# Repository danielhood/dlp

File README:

DLP - Dirty 'Lil Penguin Synth
------------------------------

- Inital conception around 2010.

- First working module was the distoriton module at the end of 2010.

- MIDI to CV module completed Feb 2012.

- Saw/Square oscillaror with 2 channel ouput mixer, mounted in toolbox completed March 2012.

- v2.0 started April 2015 which is bascially eurorack version of most of the modules

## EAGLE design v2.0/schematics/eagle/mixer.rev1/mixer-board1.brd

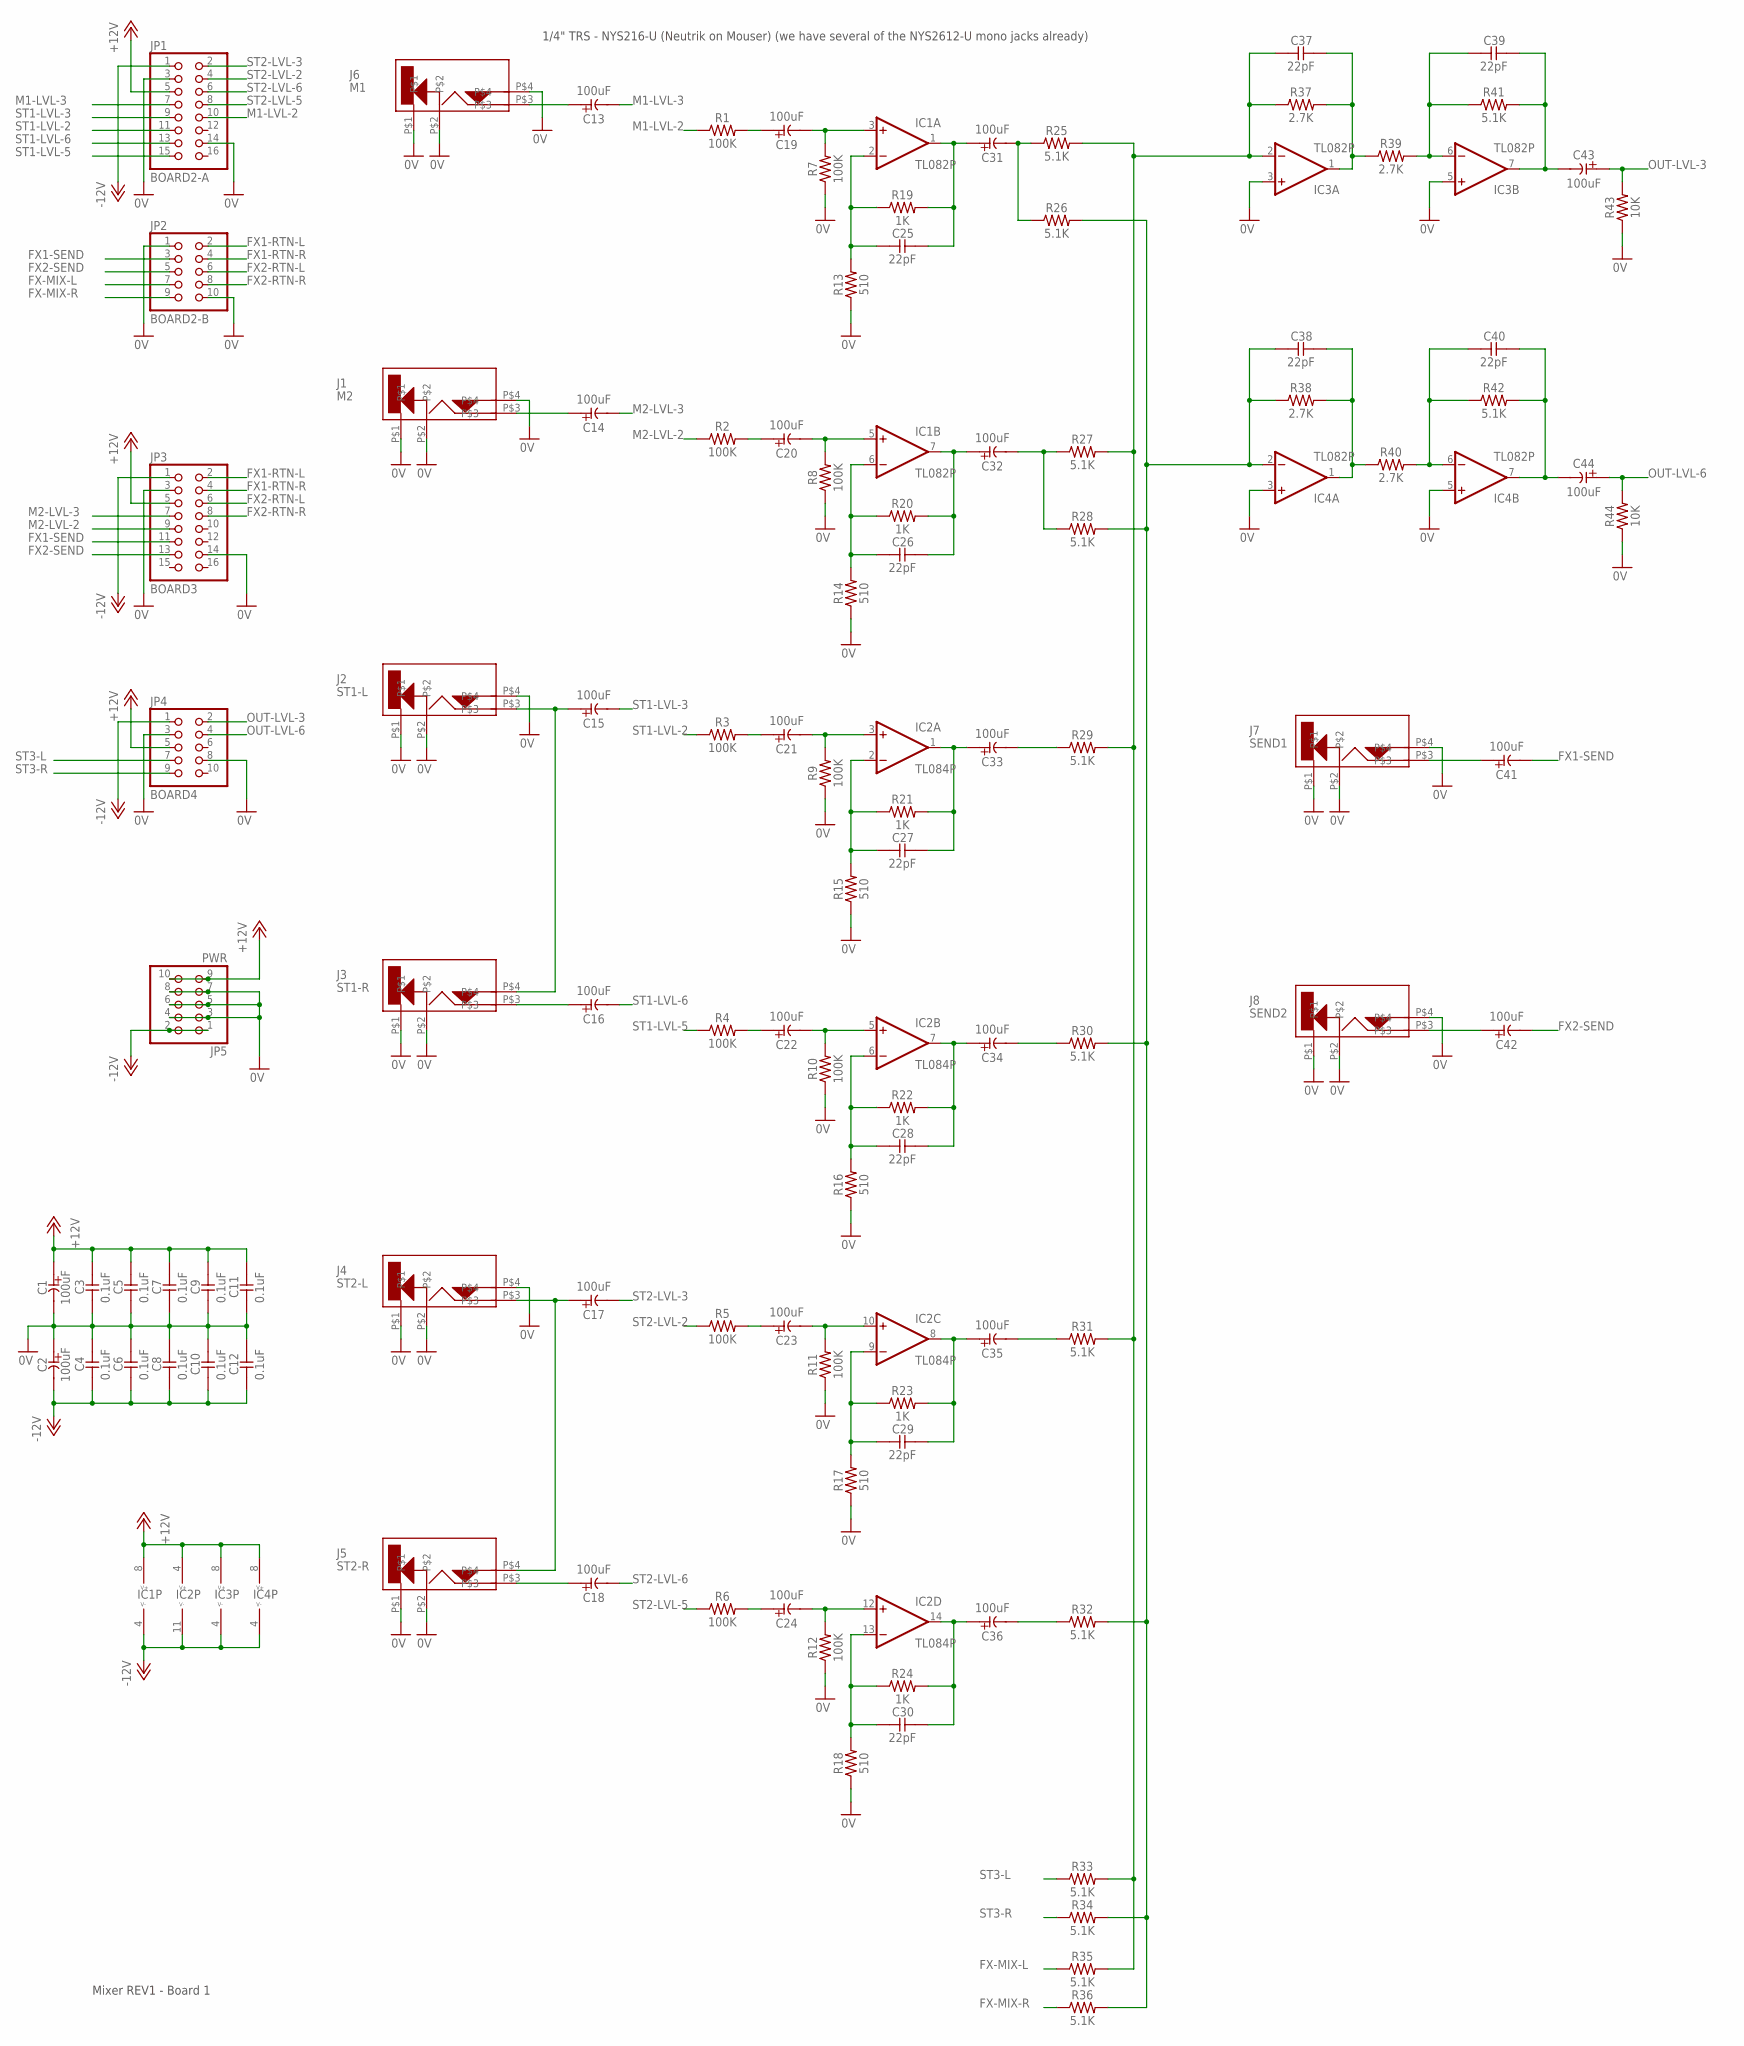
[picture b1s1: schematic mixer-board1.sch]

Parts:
C1, C2, C13, C14, C15, C16, C17, C18, C19, C20, C21, C22, C23, C24, C31, C32, C33, C34, C35, C36, C41, C42, C43, C44: 100uF; E5-8,5
C3, C4, C5, C6, C7, C8, C9, C10, C11, C12: 0.1uF; C025-024X044
C25, C26, C27, C28, C29, C30, C37, C38, C39, C40: 22pF; C025-024X044
IC1, IC3, IC4: TL082P; DIL08
IC2: TL084P; DIL14
J1: M2; CL1384
J2: ST1-L; CL1384
J3: ST1-R; CL1384
J4: ST2-L; CL1384
J5: ST2-R; CL1384
J6: M1; CL1384
J7: SEND1; CL1384
J8: SEND2; CL1384
JP1: BOARD2-A; 2X08
JP2: BOARD2-B; 2X05
JP3: BOARD3; 2X08
JP4: BOARD4; 2X05
JP5: PWR; 2X05
R1, R2, R3, R4, R5, R6, R7, R8, R9, R10, R11, R12: 100K; 0207/7
R13, R14, R15, R16, R17, R18: 510; 0207/7
R19, R20, R21, R22, R23, R24: 1K; 0207/7
R25, R26, R27, R28, R29, R30, R31, R32, R33, R34, R35, R36, R41, R42: 5.1K; 0207/7
R37, R38, R39, R40: 2.7K; 0207/7
R43, R44: 10K; 0207/7

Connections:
0V: C1.-, C2.+, C3.2, C4.1, C5.2, C6.1, C7.2, C8.1, C9.2, C10.1, C11.2, C12.1, IC3.3 (+IN), IC3.5 (+IN), IC4.3 (+IN), IC4.5 (+IN), J1.P$1, J1.P$2, J1.P$4, J2.P$1, J2.P$2, J2.P$4, J3.P$1, J3.P$2, J4.P$1, J4.P$2, J4.P$4, J5.P$1, J5.P$2, J6.P$1, J6.P$2, J6.P$4, J7.P$1, J7.P$2, J7.P$4, J8.P$1, J8.P$2, J8.P$4, JP1.3, JP1.14, JP2.1, JP2.10, JP3.3, JP3.14, JP4.3, JP4.8, JP5.3, JP5.4, JP5.5, JP5.6, JP5.7, JP5.8, R7.1, R8.1, R9.1, R10.1, R11.1, R12.1, R13.1, R14.1, R15.1, R16.1, R17.1, R18.1, R43.1, R44.1
+12V: C1.+, C3.1, C5.1, C7.1, C9.1, C11.1, IC1.8 (V+), IC2.4 (V+), IC3.8 (V+), IC4.8 (V+), JP1.5, JP3.5, JP4.5, JP5.9, JP5.10
-12V: C2.-, C4.2, C6.2, C8.2, C10.2, C12.2, IC1.4 (V-), IC2.11 (V-), IC3.4 (V-), IC4.4 (V-), JP1.1, JP3.1, JP4.1, JP5.1, JP5.2
FX1-RTN-L: JP2.2, JP3.2
FX1-RTN-R: JP2.4, JP3.4
FX1-SEND: C41.-, JP2.3, JP3.11
FX2-RTN-L: JP2.6, JP3.6
FX2-RTN-R: JP2.8, JP3.8
FX2-SEND: C42.-, JP2.5, JP3.13
FX-MIX-L: JP2.7, R35.1
FX-MIX-R: JP2.9, R36.1
M1-LVL-2: JP1.10, R1.1
M1-LVL-3: C13.-, JP1.7
M2-LVL-2: JP3.9, R2.1
M2-LVL-3: C14.-, JP3.7
unnamed: C13.+, J6.P$3
unnamed: C25.2, IC1.2 (-IN), R13.2, R19.1
unnamed: C19.-, IC1.3 (+IN), R7.2
unnamed: C19.+, R1.2
unnamed: C25.1, C31.+, IC1.1 (OUT), R19.2
unnamed: C31.-, R25.1, R26.1
unnamed: C37.2, IC3.2 (-IN), R25.2, R27.2, R29.2, R31.2, R33.2, R35.2, R37.1
unnamed: C37.1, IC3.1 (OUT), R37.2, R39.1
unnamed: C39.2, IC3.6 (-IN), R39.2, R41.1
unnamed: C32.-, R27.1, R28.1
unnamed: C38.1, IC4.1 (OUT), R38.2, R40.1
unnamed: C40.2, IC4.6 (-IN), R40.2, R42.1
unnamed: C39.1, C43.-, IC3.7 (OUT), R41.2
unnamed: C42.+, J8.P$3
unnamed: C38.2, IC4.2 (-IN), R26.2, R28.2, R30.2, R32.2, R34.2, R36.2, R38.1
unnamed: C14.+, J1.P$3
unnamed: C15.+, J2.P$3, J3.P$4
unnamed: C40.1, C44.-, IC4.7 (OUT), R42.2
unnamed: C16.+, J3.P$3
unnamed: C17.+, J4.P$3, J5.P$4
unnamed: C18.+, J5.P$3
unnamed: C26.1, C32.+, IC1.7 (OUT), R20.2
unnamed: C26.2, IC1.6 (-IN), R14.2, R20.1
unnamed: C20.-, IC1.5 (+IN), R8.2
unnamed: C20.+, R2.2
unnamed: C41.+, J7.P$3
unnamed: C34.-, R30.1
unnamed: C33.-, R29.1
unnamed: C27.1, C33.+, IC2.1 (OUT), R21.2
unnamed: C27.2, IC2.2 (-IN), R15.2, R21.1
unnamed: C21.-, IC2.3 (+IN), R9.2
unnamed: C21.+, R3.2
unnamed: C28.1, C34.+, IC2.7 (OUT), R22.2
unnamed: C28.2, IC2.6 (-IN), R16.2, R22.1
unnamed: C22.-, IC2.5 (+IN), R10.2
unnamed: C22.+, R4.2
unnamed: C35.-, R31.1
unnamed: C29.1, C35.+, IC2.8 (OUT), R23.2
unnamed: C29.2, IC2.9 (-IN), R17.2, R23.1
unnamed: C23.-, IC2.10 (+IN), R11.2
unnamed: C23.+, R5.2
unnamed: C36.-, R32.1
unnamed: C30.1, C36.+, IC2.14 (OUT), R24.2
unnamed: C30.2, IC2.13 (-IN), R18.2, R24.1
unnamed: C24.-, IC2.12 (+IN), R12.2
unnamed: C24.+, R6.2
OUT-LVL-3: C43.+, JP4.2, R43.2
OUT-LVL-6: C44.+, JP4.4, R44.2
ST1-LVL-2: JP1.11, R3.1
ST1-LVL-3: C15.-, JP1.9
ST1-LVL-5: JP1.15, R4.1
ST1-LVL-6: C16.-, JP1.13
ST2-LVL-2: JP1.4, R5.1
ST2-LVL-3: C17.-, JP1.2
ST2-LVL-5: JP1.8, R6.1
ST2-LVL-6: C18.-, JP1.6
ST3-L: JP4.7, R33.1
ST3-R: JP4.9, R34.1

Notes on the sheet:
1/4" TRS - NYS216-U (Neutrik on Mouser) (we have several of the NYS2612-U mono jacks already)
Mixer REV1 - Board 1

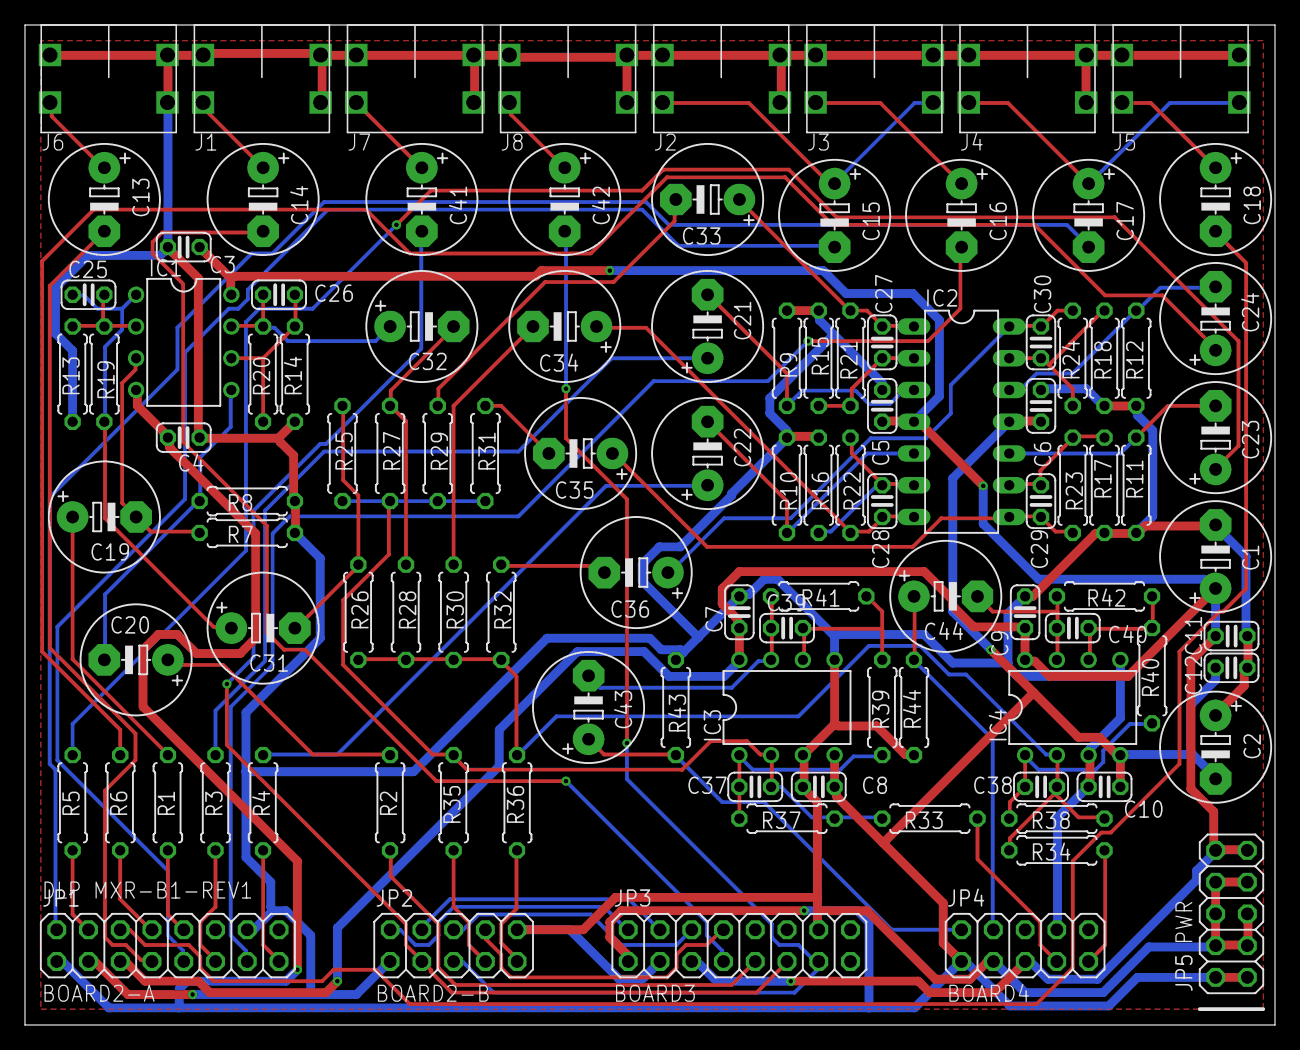
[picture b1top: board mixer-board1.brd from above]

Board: 2 copper layers, 100.0 x 80.0 mm, 105 parts (0 on the bottom side), 73 nets.

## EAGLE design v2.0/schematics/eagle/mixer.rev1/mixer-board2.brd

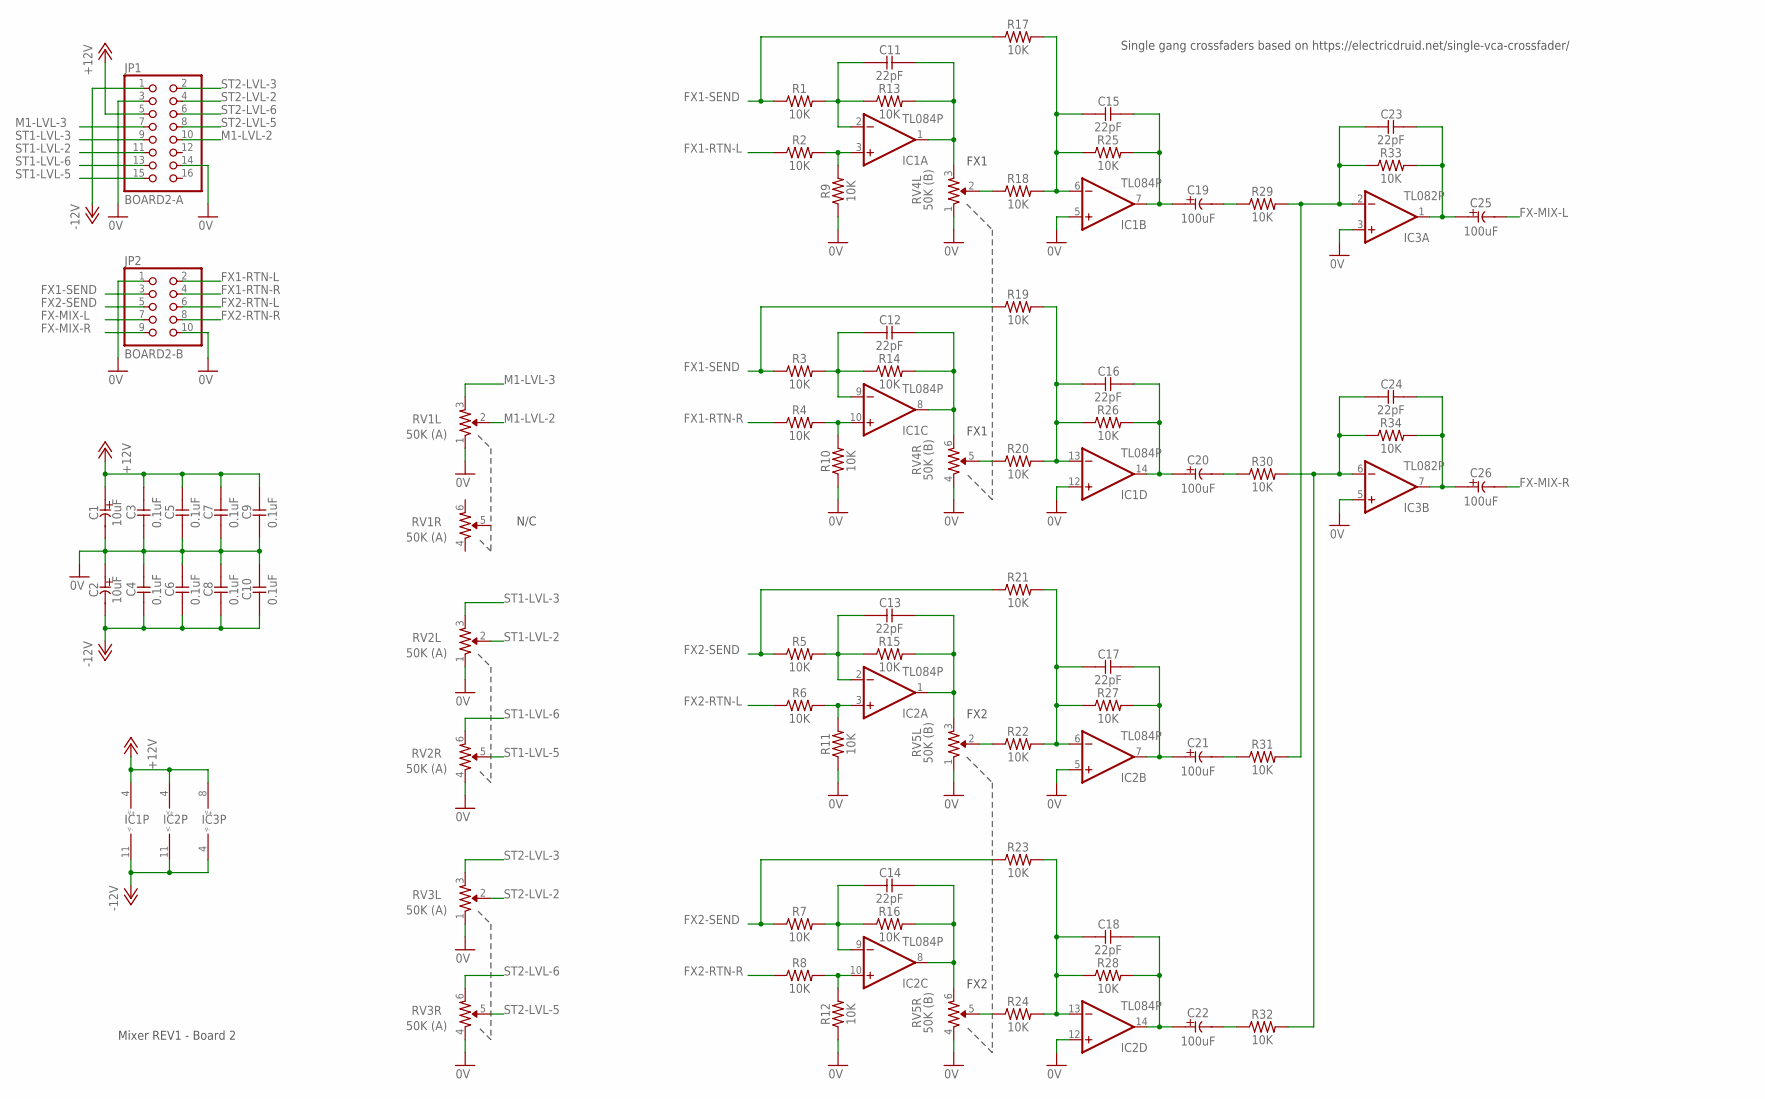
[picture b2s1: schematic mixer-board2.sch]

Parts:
C1, C2: 10uF; E2-5
C3, C4, C5, C6, C7, C8, C9, C10: 0.1uF; C025-024X044
C11, C12, C13, C14, C15, C16, C17, C18, C23, C24: 22pF; C025-024X044
C19, C20, C21, C22, C25, C26: 100uF; E5-8,5
IC1, IC2: TL084P; DIL14
IC3: TL082P; DIL08
JP1: BOARD2-A; 2X08
JP2: BOARD2-B; 2X05
R1, R2, R3, R4, R5, R6, R7, R8, R9, R10, R11, R12, R13, R14, R15, R16, R17, R18, R19, R20, R21, R22, R23, R24, R25, R26, R27, R28, R29, R30, R31, R32, R33, R34: 10K; 0207/7
RV1, RV2, RV3: 50K (A); _COMMON_3RP/1610G
RV4, RV5: 50K (B); _COMMON_3RP/1610G

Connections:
0V: C1.-, C2.+, C3.2, C4.1, C5.2, C6.1, C7.2, C8.1, C9.2, C10.1, IC1.5 (+IN), IC1.12 (+IN), IC2.5 (+IN), IC2.12 (+IN), IC3.3 (+IN), IC3.5 (+IN), JP1.3, JP1.14, JP2.1, JP2.10, R9.1, R10.1, R11.1, R12.1, RV1.1, RV2.1, RV2.4 (1), RV3.1, RV3.4 (1), RV4.1, RV4.4 (1), RV5.1, RV5.4 (1)
+12V: C1.+, C3.1, C5.1, C7.1, C9.1, IC1.4 (V+), IC2.4 (V+), IC3.8 (V+), JP1.5
-12V: C2.-, C4.2, C6.2, C8.2, C10.2, IC1.11 (V-), IC2.11 (V-), IC3.4 (V-), JP1.1
FX1-RTN-L: JP2.2, R2.1
FX1-RTN-R: JP2.4, R4.1
FX1-SEND: JP2.3, R1.1, R3.1, R17.1, R19.1
FX2-RTN-L: JP2.6, R6.1
FX2-RTN-R: JP2.8, R8.1
FX2-SEND: JP2.5, R5.1, R7.1, R21.1, R23.1
FX-MIX-L: C25.-, JP2.7
FX-MIX-R: C26.-, JP2.9
M1-LVL-2: JP1.10, RV1.2
M1-LVL-3: JP1.7, RV1.3
unnamed: C11.1, IC1.1 (OUT), R13.2, RV4.3
unnamed: R18.1, RV4.2
unnamed: C15.2, IC1.6 (-IN), R17.2, R18.2, R25.1
unnamed: C15.1, C19.+, IC1.7 (OUT), R25.2
unnamed: C12.2, IC1.9 (-IN), R3.2, R14.1
unnamed: R20.1, RV4.5 (2)
unnamed: C11.2, IC1.2 (-IN), R1.2, R13.1
unnamed: IC1.3 (+IN), R2.2, R9.2
unnamed: C19.-, R29.1
unnamed: C23.1, C25.+, IC3.1 (OUT), R33.2
unnamed: C12.1, IC1.8 (OUT), R14.2, RV4.6 (3)
unnamed: C13.1, IC2.1 (OUT), R15.2, RV5.3
unnamed: R22.1, RV5.2
unnamed: IC1.10 (+IN), R4.2, R10.2
unnamed: C16.2, IC1.13 (-IN), R19.2, R20.2, R26.1
unnamed: C16.1, C20.+, IC1.14 (OUT), R26.2
unnamed: C17.2, IC2.6 (-IN), R21.2, R22.2, R27.1
unnamed: C20.-, R30.1
unnamed: C17.1, C21.+, IC2.7 (OUT), R27.2
unnamed: C24.1, C26.+, IC3.7 (OUT), R34.2
unnamed: C13.2, IC2.2 (-IN), R5.2, R15.1
unnamed: IC2.3 (+IN), R6.2, R11.2
unnamed: C21.-, R31.1
unnamed: C23.2, IC3.2 (-IN), R29.2, R31.2, R33.1
unnamed: C14.2, IC2.9 (-IN), R7.2, R16.1
unnamed: C14.1, IC2.8 (OUT), R16.2, RV5.6 (3)
unnamed: IC2.10 (+IN), R8.2, R12.2
unnamed: R24.1, RV5.5 (2)
unnamed: C18.2, IC2.13 (-IN), R23.2, R24.2, R28.1
unnamed: C18.1, C22.+, IC2.14 (OUT), R28.2
unnamed: C22.-, R32.1
unnamed: C24.2, IC3.6 (-IN), R30.2, R32.2, R34.1
ST1-LVL-2: JP1.11, RV2.2
ST1-LVL-3: JP1.9, RV2.3
ST1-LVL-5: JP1.15, RV2.5 (2)
ST1-LVL-6: JP1.13, RV2.6 (3)
ST2-LVL-2: JP1.4, RV3.2
ST2-LVL-3: JP1.2, RV3.3
ST2-LVL-5: JP1.8, RV3.5 (2)
ST2-LVL-6: JP1.6, RV3.6 (3)

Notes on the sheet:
N/C
Single gang crossfaders based on https://electricdruid.net/single-vca-crossfader/
FX1
FX2
Mixer REV1 - Board 2

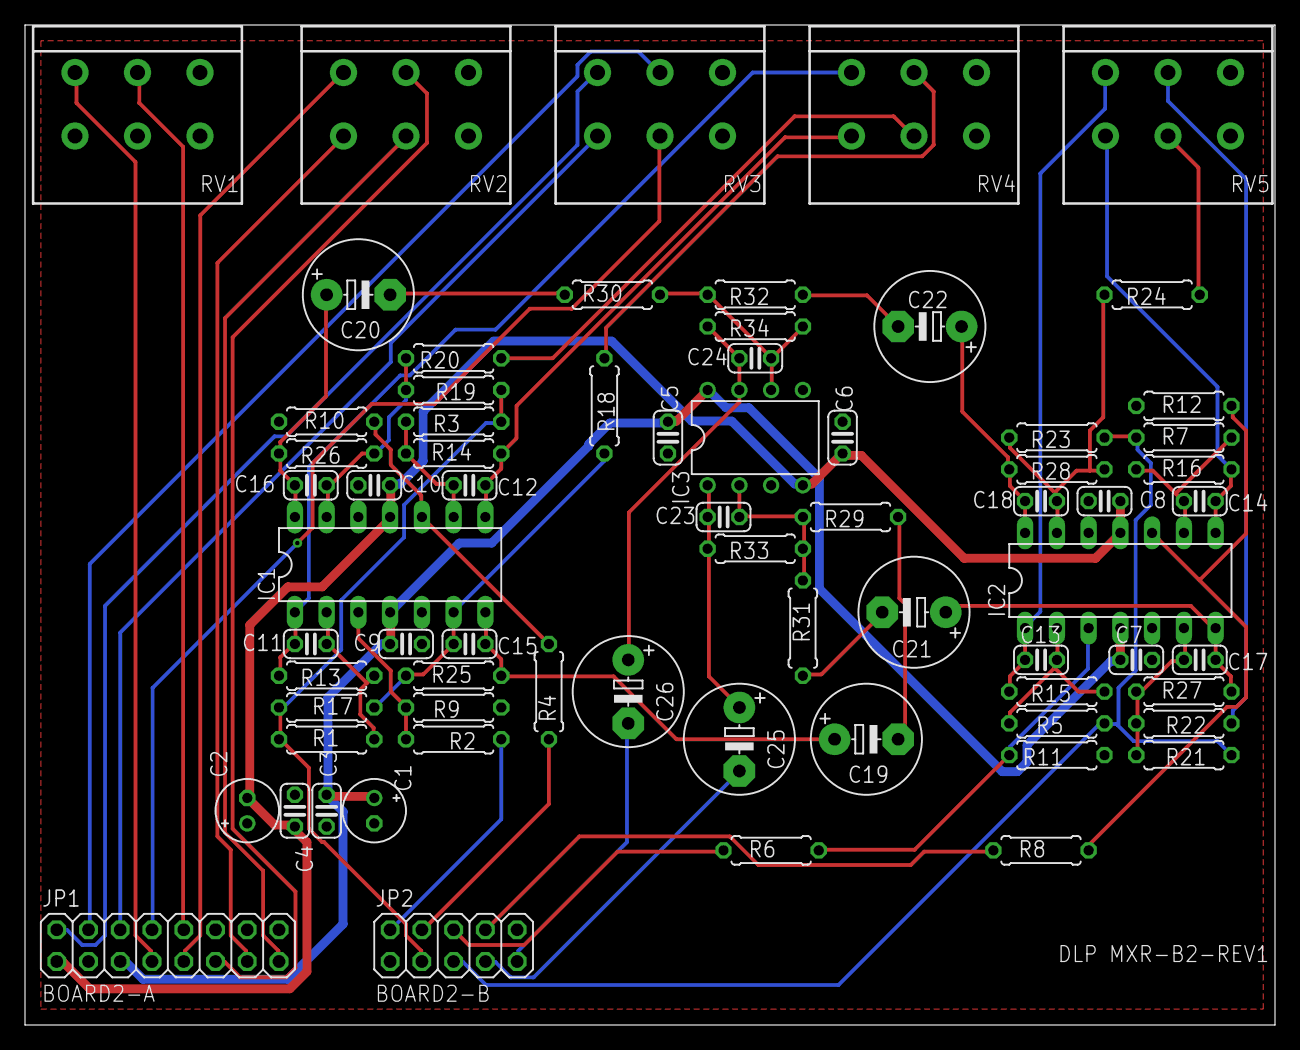
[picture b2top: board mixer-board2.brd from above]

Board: 2 copper layers, 100.0 x 80.0 mm, 70 parts (0 on the bottom side), 53 nets.

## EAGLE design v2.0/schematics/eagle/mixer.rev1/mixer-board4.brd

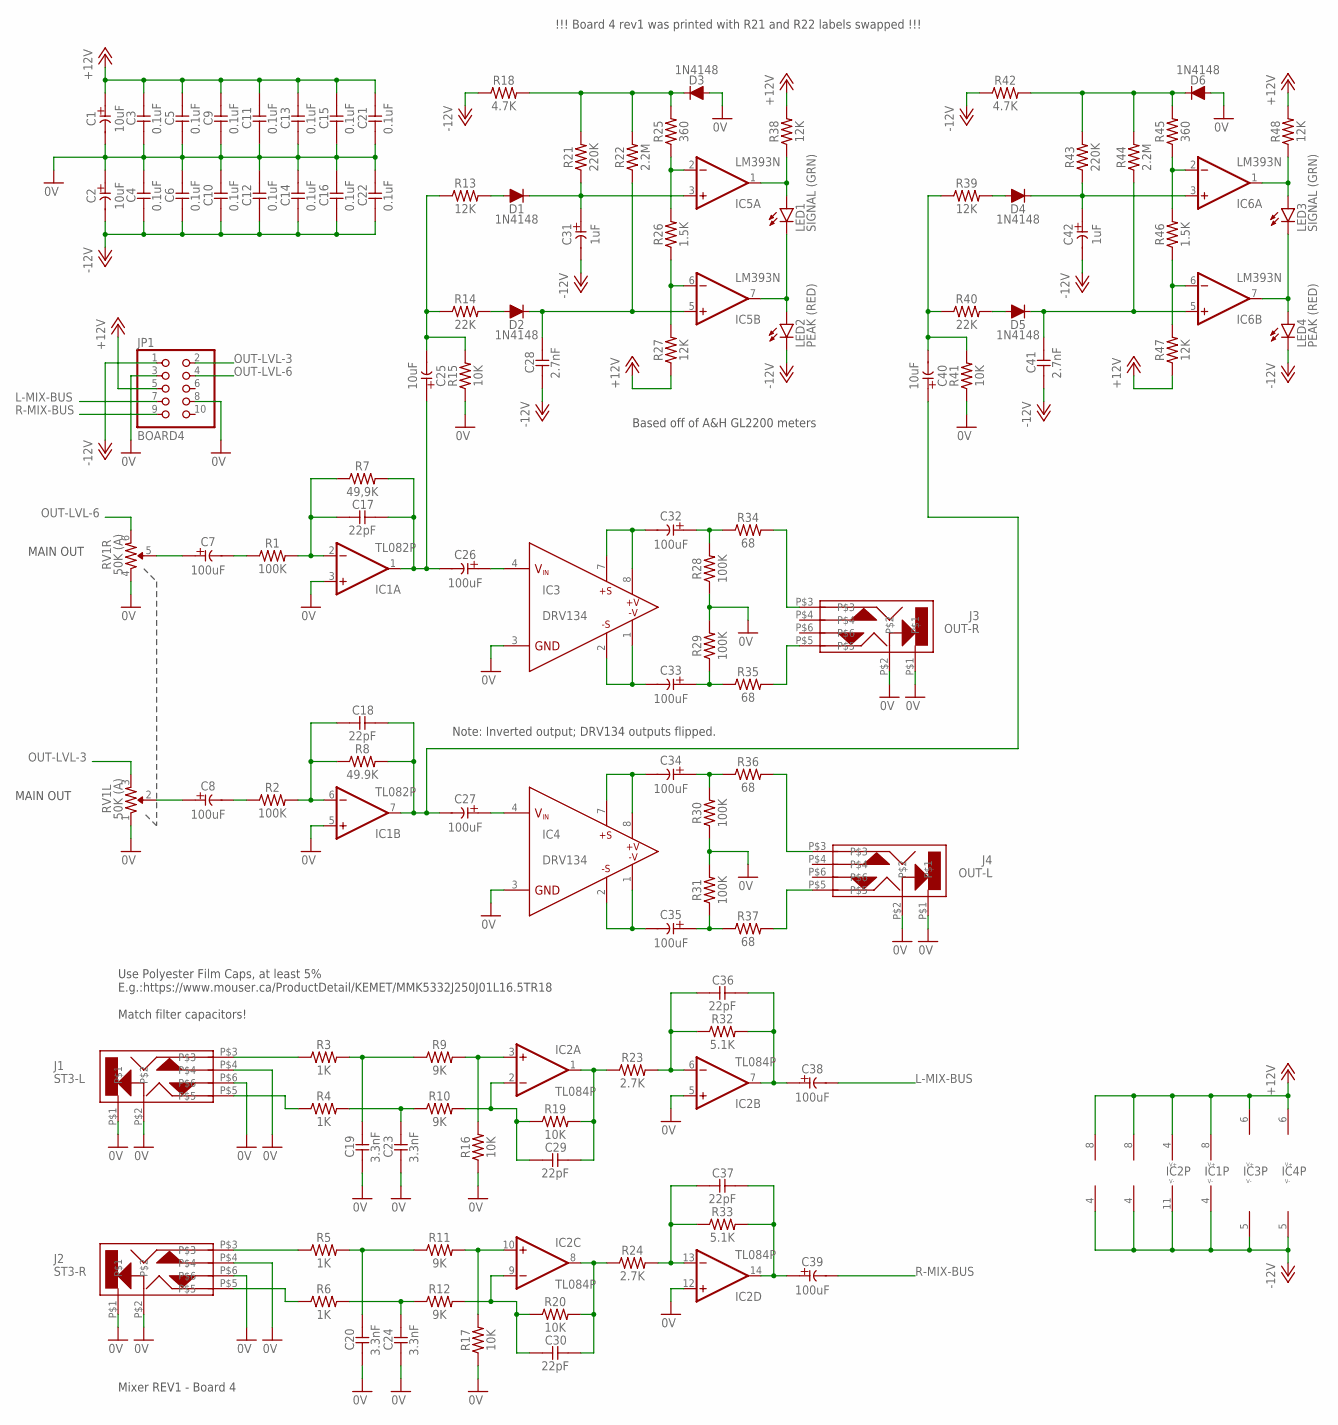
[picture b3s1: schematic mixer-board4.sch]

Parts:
C1, C2, C25, C40: 10uF; E2-5
C3, C4, C5, C6, C9, C10, C11, C12, C13, C14, C15, C16, C21, C22: 0.1uF; C025-024X044
C7, C8, C26, C27, C32, C33, C34, C35, C38, C39: 100uF; E5-8,5
C17, C18, C29, C30, C36, C37: 22pF; C025-024X044
C19, C20, C23, C24: 3.3nF; C050-024X044
C28, C41: 2.7nF; C025-024X044
C31, C42: 1uF; E2-5
D1, D2, D3, D4, D5, D6: 1N4148; DO34-5
IC1: TL082P; DIL08
IC2: TL084P; DIL14
IC3, IC4: DRV134; DIL08
IC5, IC6: LM393N; DIL08
J1: ST3-L; NYS216-U
J2: ST3-R; NYS216-U
J3: OUT-R; NYS216-U
J4: OUT-L; NYS216-U
JP1: BOARD4; 2X05
LED1, LED3: SIGNAL (GRN); LED3MM
LED2, LED4: PEAK (RED); LED3MM
R1, R2, R28, R29, R30, R31: 100K; 0207/7
R3, R4, R5, R6: 1K; 0207/7
R7: 49,9K; 0207/7
R8: 49.9K; 0207/7
R9, R10, R11, R12: 9K; 0207/7
R13, R27, R38, R39, R47, R48: 12K; 0207/7
R14, R40: 22K; 0207/7
R15, R16, R17, R19, R20, R41: 10K; 0207/7
R18, R42: 4.7K; 0207/7
R21, R43: 220K; 0207/7
R22, R44: 2.2M; 0207/7
R23, R24: 2.7K; 0207/7
R25, R45: 360; 0207/7
R26, R46: 1.5K; 0207/7
R32, R33: 5.1K; 0207/7
R34, R35, R36, R37: 68; 0207/7
RV1: 50K (A); _COMMON_3RP/1610G

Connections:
0V: C1.-, C2.+, C3.2, C4.1, C5.2, C6.1, C9.2, C10.1, C11.2, C12.1, C13.2, C14.1, C15.2, C16.1, C19.2, C20.2, C21.2, C22.1, C23.2, C24.2, D3.A, D6.A, IC1.3 (+IN), IC1.5 (+IN), IC2.5 (+IN), IC2.12 (+IN), IC3.3 (GND), IC4.3 (GND), J1.P$1, J1.P$2, J1.P$4, J1.P$6, J2.P$1, J2.P$2, J2.P$4, J2.P$6, J3.P$1, J3.P$2, J4.P$1, J4.P$2, JP1.3, JP1.8, R15.1, R16.1, R17.1, R28.1, R29.2, R30.1, R31.2, R41.1, RV1.1, RV1.4 (1)
+12V: C1.+, C3.1, C5.1, C9.1, C11.1, C13.1, C15.1, C21.1, IC1.8 (V+), IC2.4 (V+), IC3.6 (V+), IC4.6 (V+), IC5.8 (V+), IC6.8 (V+), JP1.5, R27.1, R38.2, R47.1, R48.2
-12V: C2.-, C4.2, C6.2, C10.2, C12.2, C14.2, C16.2, C22.2, C28.2, C31.-, C41.2, C42.-, IC1.4 (V-), IC2.11 (V-), IC3.5 (V-), IC4.5 (V-), IC5.4 (V-), IC6.4 (V-), JP1.1, LED2.K (C), LED4.K (C), R18.1, R42.1
L-MIX-BUS: C38.-, JP1.7
unnamed: J2.P$3, R5.1
unnamed: C20.1, R5.2, R11.1
unnamed: IC2.10 (+IN), R11.2, R17.2
unnamed: C24.1, R6.2, R12.1
unnamed: C30.2, IC2.9 (-IN), R12.2, R20.1
unnamed: J2.P$5, R6.1
unnamed: C37.2, IC2.13 (-IN), R24.2, R33.1
unnamed: C30.1, IC2.8 (OUT), R20.2, R24.1
unnamed: J1.P$3, R3.1
unnamed: C37.1, C39.+, IC2.14 (OUT), R33.2
unnamed: C19.1, R3.2, R9.1
unnamed: IC2.3 (+IN), R9.2, R16.2
unnamed: C29.1, IC2.1 (OUT), R19.2, R23.1
unnamed: C36.2, IC2.6 (-IN), R23.2, R32.1
unnamed: C36.1, C38.+, IC2.7 (OUT), R32.2
unnamed: C23.1, R4.2, R10.1
unnamed: J1.P$5, R4.1
unnamed: C29.2, IC2.2 (-IN), R10.2, R19.1
unnamed: C7.+, RV1.5 (2)
unnamed: C17.1, C25.+, C26.-, IC1.1 (OUT), R7.2
unnamed: C8.+, RV1.2
unnamed: C17.2, IC1.2 (-IN), R1.2, R7.1
unnamed: C8.-, R2.1
unnamed: C18.2, IC1.6 (-IN), R2.2, R8.1
unnamed: C18.1, C27.-, C40.+, IC1.7 (OUT), R8.2
unnamed: C7.-, R1.1
unnamed: C32.-, IC3.7 (+SENSE), IC3.8 (+V0)
unnamed: C33.-, IC3.1 (-V0), IC3.2 (-SENSE)
unnamed: J4.P$3, R36.2
unnamed: J4.P$5, R37.2
unnamed: J3.P$5, R35.2
unnamed: C26.+, IC3.4 (VIN)
unnamed: C27.+, IC4.4 (VIN)
unnamed: J3.P$3, R34.2
unnamed: C35.-, IC4.1 (-V0), IC4.2 (-SENSE)
unnamed: C34.-, IC4.7 (+SENSE), IC4.8 (+V0)
unnamed: C34.+, R30.2, R36.1
unnamed: C35.+, R31.1, R37.1
unnamed: C33.+, R29.1, R35.1
unnamed: C32.+, R28.2, R34.1
unnamed: C25.-, R13.1, R14.1, R15.2
unnamed: D2.A, R14.2
unnamed: D1.A, R13.2
unnamed: C31.+, D1.C, IC5.3 (+IN), R21.1
unnamed: C28.1, D2.C, IC5.5 (+IN), R22.1
unnamed: IC5.6 (-IN), R26.1, R27.2
unnamed: IC5.2 (-IN), R25.1, R26.2
unnamed: D3.C, R18.2, R21.2, R22.2, R25.2
unnamed: IC5.1 (OUT), LED1.A, R38.1
unnamed: IC5.7 (OUT), LED1.K (C), LED2.A
unnamed: C40.-, R39.1, R40.1, R41.2
unnamed: D5.A, R40.2
unnamed: D4.A, R39.2
unnamed: C42.+, D4.C, IC6.3 (+IN), R43.1
unnamed: C41.1, D5.C, IC6.5 (+IN), R44.1
unnamed: IC6.6 (-IN), R46.1, R47.2
unnamed: IC6.2 (-IN), R45.1, R46.2
unnamed: D6.C, R42.2, R43.2, R44.2, R45.2
unnamed: IC6.1 (OUT), LED3.A, R48.1
unnamed: IC6.7 (OUT), LED3.K (C), LED4.A
OUT-LVL-3: JP1.2, RV1.3
OUT-LVL-6: JP1.4, RV1.6 (3)
R-MIX-BUS: C39.-, JP1.9

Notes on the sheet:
Use Polyester Film Caps, at least 5% E.g.:https://www.mouser.ca/ProductDetail/KEMET/MMK5332J250J01L16.5TR18 Match filter capacitors!
MAIN OUT
Based off of A&H GL2200 meters
Note: Inverted output; DRV134 outputs flipped.
Mixer REV1 - Board 4
!!! Board 4 rev1 was printed with R21 and R22 labels swapped !!!

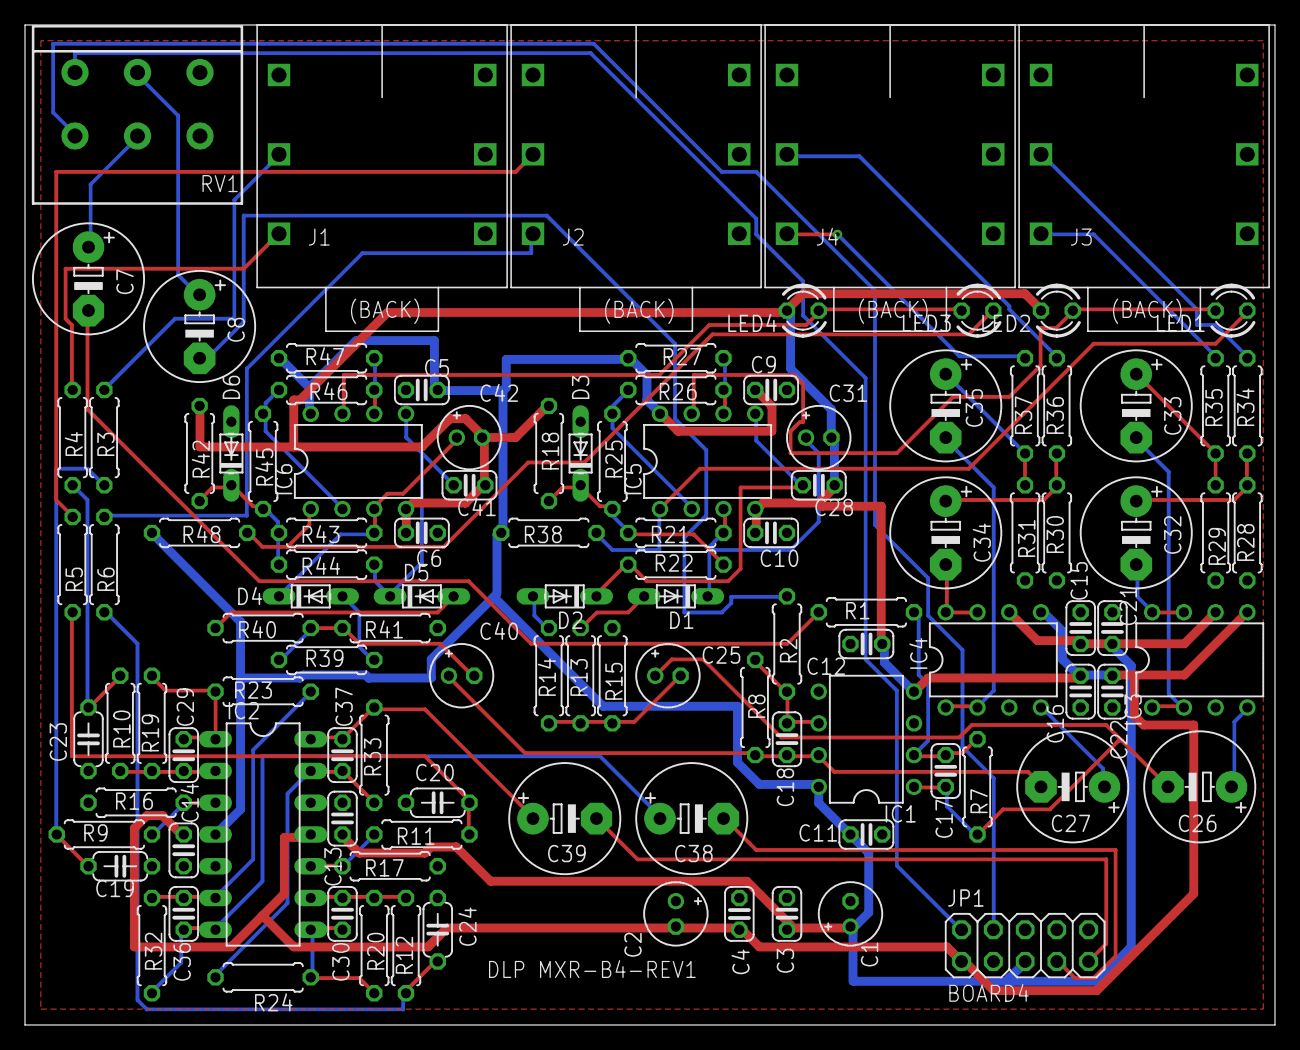
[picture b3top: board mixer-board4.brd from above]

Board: 2 copper layers, 100.0 x 80.0 mm, 112 parts (0 on the bottom side), 67 nets.

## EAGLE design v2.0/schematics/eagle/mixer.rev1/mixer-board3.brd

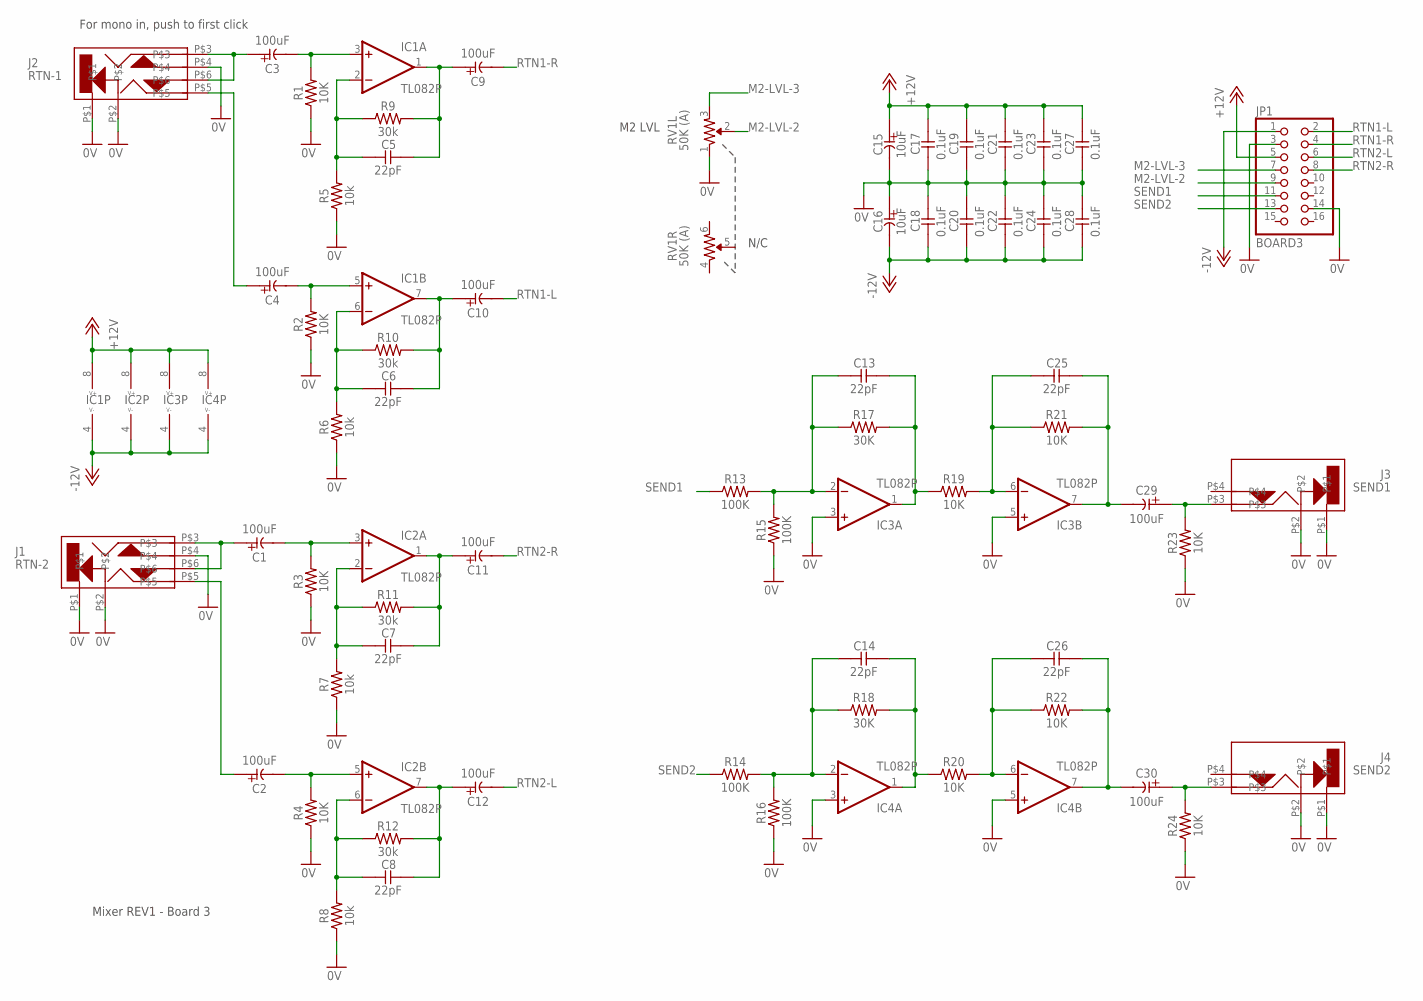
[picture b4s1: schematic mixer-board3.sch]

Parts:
C1, C2, C3, C4, C9, C10, C11, C12, C29, C30: 100uF; E5-8,5
C5, C6, C7, C8, C13, C14, C25, C26: 22pF; C025-024X044
C15, C16: 10uF; E2-5
C17, C18, C19, C20, C21, C22, C23, C24, C27, C28: 0.1uF; C025-024X044
IC1, IC2, IC3, IC4: TL082P; DIL08
J1: RTN-2; NYS216-U
J2: RTN-1; NYS216-U
J3: SEND1; NYS2162-U
J4: SEND2; NYS2162-U
JP1: BOARD3; 2X08
R1, R2, R3, R4, R19, R20, R21, R22, R23, R24: 10K; 0207/7
R5, R6, R7, R8: 10k; 0207/7
R9, R10, R11, R12: 30k; 0207/7
R13, R14, R15, R16: 100K; 0207/7
R17, R18: 30K; 0207/7
RV1: 50K (A); _COMMON_3RP/1610G

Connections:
0V: C15.-, C16.+, C17.2, C18.1, C19.2, C20.1, C21.2, C22.1, C23.2, C24.1, C27.2, C28.1, IC3.3 (+IN), IC3.5 (+IN), IC4.3 (+IN), IC4.5 (+IN), J1.P$1, J1.P$2, J1.P$4, J2.P$1, J2.P$2, J2.P$4, J3.P$1, J3.P$2, J4.P$1, J4.P$2, JP1.3, JP1.14, R1.1, R2.1, R3.1, R4.1, R5.1, R6.1, R7.1, R8.1, R15.1, R16.1, R23.1, R24.1, RV1.1
+12V: C15.+, C17.1, C19.1, C21.1, C23.1, C27.1, IC1.8 (V+), IC2.8 (V+), IC3.8 (V+), IC4.8 (V+), JP1.5
-12V: C16.-, C18.2, C20.2, C22.2, C24.2, C28.2, IC1.4 (V-), IC2.4 (V-), IC3.4 (V-), IC4.4 (V-), JP1.1
M2-LVL-2: JP1.9, RV1.2
M2-LVL-3: JP1.7, RV1.3
unnamed: C3.+, J2.P$3, J2.P$6
unnamed: C4.+, J2.P$5
unnamed: C6.2, IC1.6 (-IN), R6.2, R10.1
unnamed: C6.1, C10.+, IC1.7 (OUT), R10.2
unnamed: C3.-, IC1.3 (+IN), R1.2
unnamed: C5.2, IC1.2 (-IN), R5.2, R9.1
unnamed: C5.1, C9.+, IC1.1 (OUT), R9.2
unnamed: C4.-, IC1.5 (+IN), R2.2
unnamed: C7.2, IC2.2 (-IN), R7.2, R11.1
unnamed: C7.1, C11.+, IC2.1 (OUT), R11.2
unnamed: C1.-, IC2.3 (+IN), R3.2
unnamed: C2.-, IC2.5 (+IN), R4.2
unnamed: C8.2, IC2.6 (-IN), R8.2, R12.1
unnamed: C8.1, C12.+, IC2.7 (OUT), R12.2
unnamed: C1.+, J1.P$3, J1.P$6
unnamed: C2.+, J1.P$5
unnamed: C13.2, IC3.2 (-IN), R13.2, R15.2, R17.1
unnamed: C13.1, IC3.1 (OUT), R17.2, R19.1
unnamed: C25.2, IC3.6 (-IN), R19.2, R21.1
unnamed: C25.1, C29.-, IC3.7 (OUT), R21.2
unnamed: C14.2, IC4.2 (-IN), R14.2, R16.2, R18.1
unnamed: C14.1, IC4.1 (OUT), R18.2, R20.1
unnamed: C26.2, IC4.6 (-IN), R20.2, R22.1
unnamed: C26.1, C30.-, IC4.7 (OUT), R22.2
OUT-LVL-1: C30.+, J4.P$3, R24.2
OUT-LVL-6: C29.+, J3.P$3, R23.2
RTN1-L: C10.-, JP1.2
RTN1-R: C9.-, JP1.4
RTN2-L: C12.-, JP1.6
RTN2-R: C11.-, JP1.8
SEND1: JP1.11, R13.1
SEND2: JP1.13, R14.1

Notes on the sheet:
N/C
For mono in, push to first click
M2 LVL
Mixer REV1 - Board 3

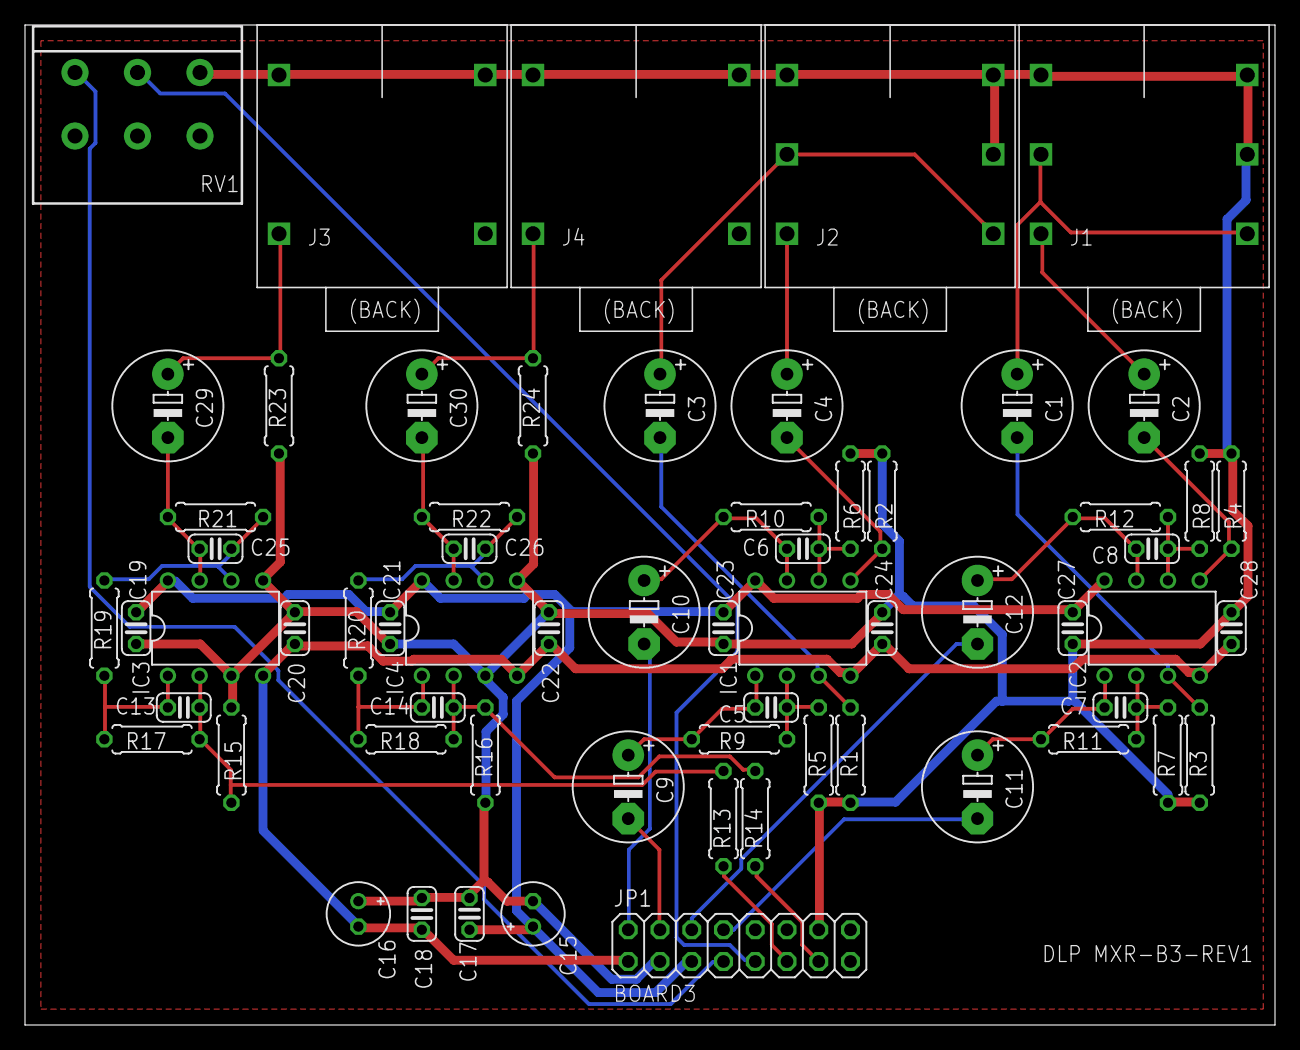
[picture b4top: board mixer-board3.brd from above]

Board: 2 copper layers, 100.0 x 80.0 mm, 64 parts (0 on the bottom side), 37 nets.
